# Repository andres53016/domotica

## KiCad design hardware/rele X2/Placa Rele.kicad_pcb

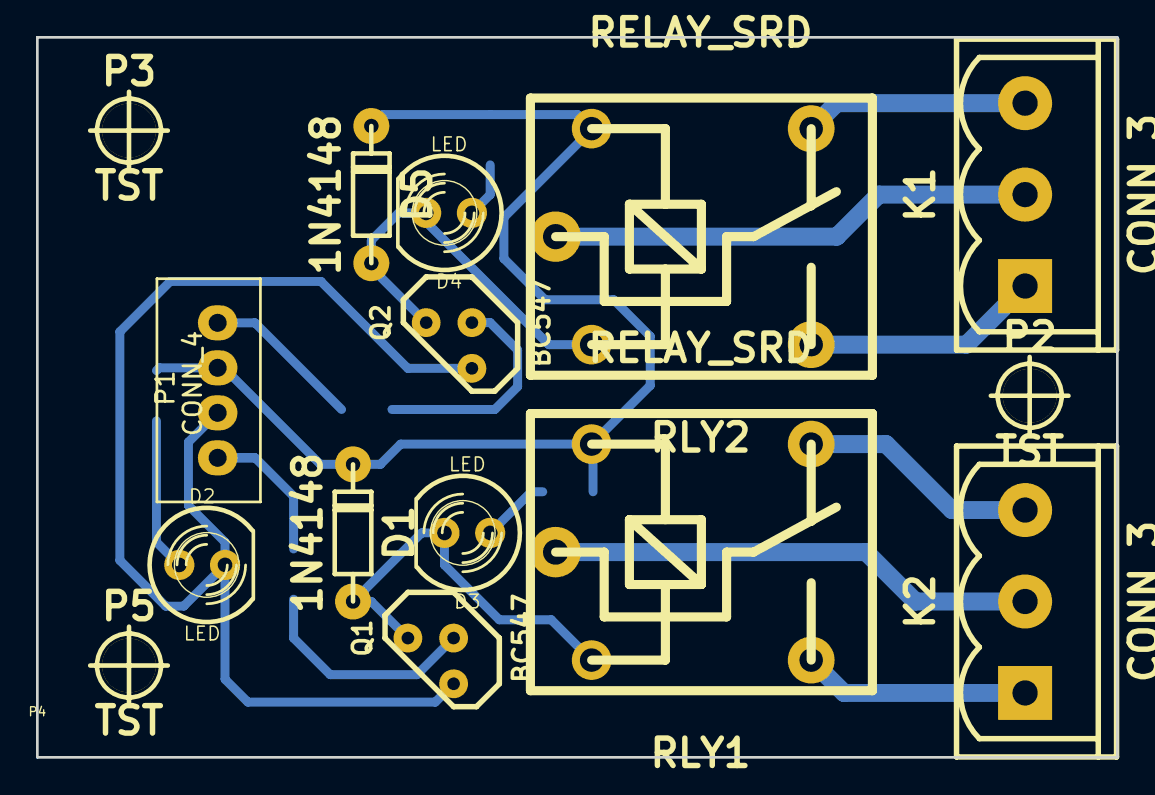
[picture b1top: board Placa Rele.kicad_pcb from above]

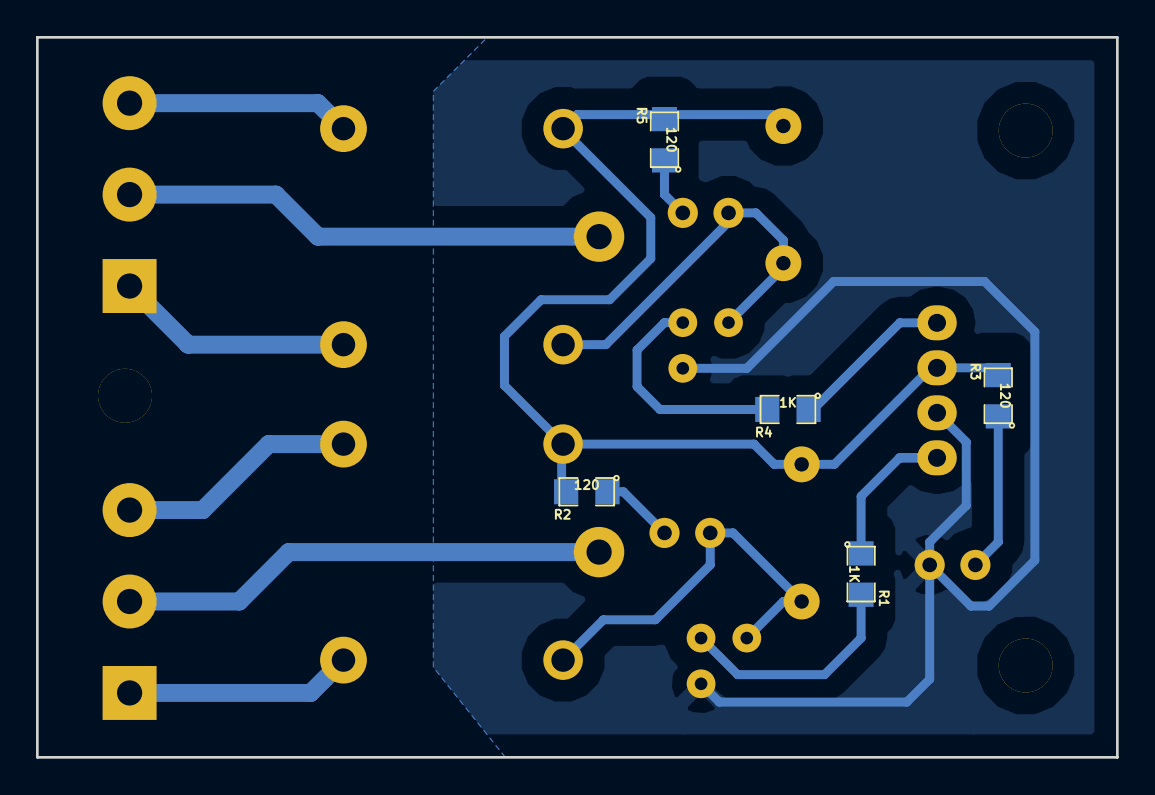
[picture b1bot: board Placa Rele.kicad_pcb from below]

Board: 2 copper layers, 60.0 x 40.0 mm, 21 parts (5 on the bottom side), 17 nets.

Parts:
D1, D5: 1N4148; diode_do35
D2, D3, D4: LED; LED-5MM
K1, K2: CONN_3; mstbva_2,5/3-g-5,08
P1: CONN_4; B4B-XH-A
P2, P3, P5: TST; hole_3mm
P4: TST; PLACA
Q1, Q2: BC547; TO92-123
R1, R4: 1K; SM0805LarguePads
R2, R3, R5: 120; SM0805LarguePads
RLY1, RLY2: RELAY_SRD; relay_SRD

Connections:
GND: D2.2, P1.2, Q1.3, Q2.3
unnamed: D4.1, R5.1
unnamed: Q2.2, R4.2
unnamed: D4.2, D5.1, Q2.1, RLY2.2
unnamed: K2.3, RLY1.4
unnamed: K2.1, RLY1.3
unnamed: K1.2, RLY2.1
unnamed: K1.3, RLY2.4
unnamed: K2.2, RLY1.1
unnamed: K1.1, RLY2.3
unnamed: D2.1, R3.1
unnamed: Q1.2, R1.2
unnamed: D1.1, D3.2, Q1.1, RLY1.2
unnamed: D3.1, R2.1
Relay 1: P1.1, R1.1
Relay 2: P1.4, R4.1
VCC: D1.2, D5.2, P1.3, R2.2, R3.2, R5.2, RLY1.5, RLY2.5

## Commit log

2014-10-24 funcional falta mejorar el codigo
2014-11-20 se agrego el hardware
